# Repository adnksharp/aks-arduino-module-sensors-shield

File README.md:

# AKS AMSS | Arduino Module Sensors Shield

Shield configurable para modulos de sensores de Arduino a cajas de contactos

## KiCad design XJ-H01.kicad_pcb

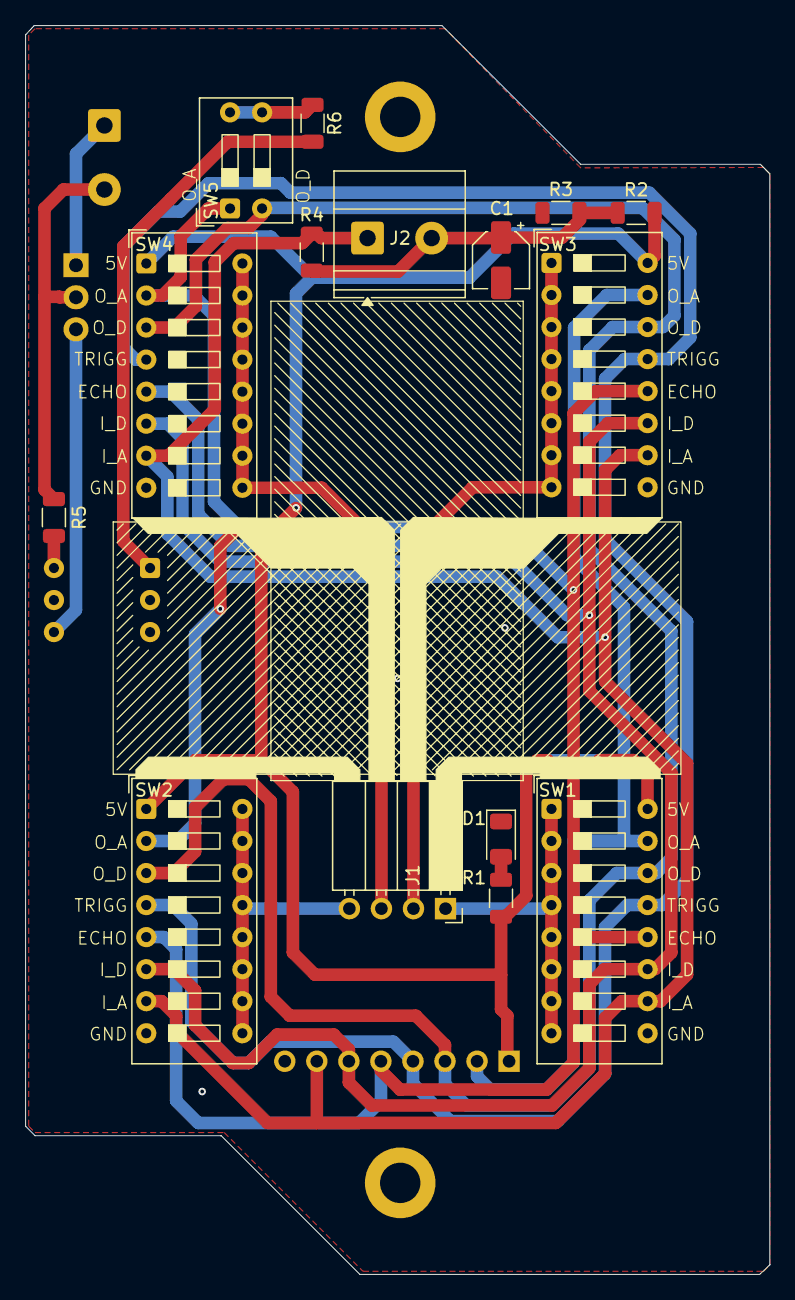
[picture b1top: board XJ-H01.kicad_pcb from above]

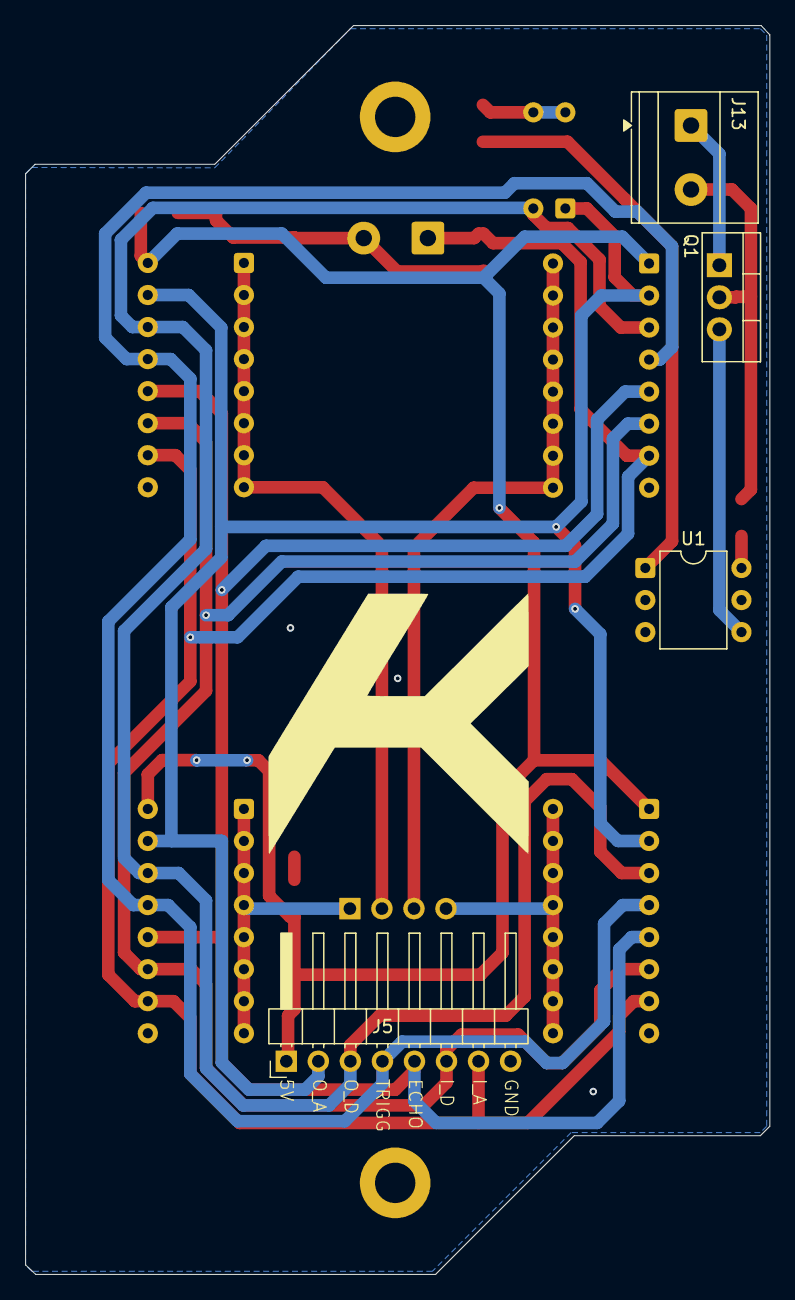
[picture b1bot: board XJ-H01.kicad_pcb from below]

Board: 2 copper layers, 59.0 x 99.0 mm, 22 parts (5 on the bottom side), 20 nets.

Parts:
C1: 47u; CP_Elec_4x3.9
D1: LED; LED_1206_3216Metric
G0: LOGO; logog
J1: 01x04; PinSocket_1x04_P2.54mm_Horizontal
J2: SCT_013; TerminalBlock_Phoenix_MKDS-1,5-2-5.08_1x02_P5.08mm_Horizont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
J5: P_01x08; PinHeader_1x08_P2.54mm_Horizontal
J13: AC; TerminalBlock_Phoenix_MKDS-1,5-2-5.08_1x02_P5.08mm_Horizont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
MX1, MX2: MountingHole_3.2mm_M3_DIN965_Pad
Q1: BT139-600; TO-220-3_Vertical
R1: 220; R_1206_3216Metric
R2, R3: 10k; R_1206_3216Metric
R4, R6: 330; R_1206_3216Metric
R5: 180; R_1206_3216Metric
SW1, SW2, SW3, SW4: SW_DIP_x08; SW_DIP_SPSTx08_Slide_9.78x22.5mm_W7.62mm_P2.54mm
SW5: SW_DIP_x02; SW_DIP_SPSTx02_Slide_9.78x7.26mm_W7.62mm_P2.54mm
U1: MOC3011M; DIP-6_W7.62mm

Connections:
+5V: J5.1, R1.2, R2.2, SW1.16, SW2.1, SW3.16, SW4.1
AC_L: J13.1, Q1.1 (A1)
AC_SW: J13.2, Q1.2 (A2), R5.2
Earth: C1.2, D1.1 (K), J5.8, R3.1, SW1.9, SW2.8, SW3.9, SW4.8, U1.2
I_A: J2.1, J5.7, R4.2, SW1.10, SW2.7, SW3.10, SW4.7
I_D: J5.6, SW1.11, SW2.6, SW3.11, SW4.6
LB: C1.1, J2.2, R2.1, R3.2, R4.1
unnamed: D1.2 (A), R1.1
unnamed: J1.1, SW1.1, SW1.2, SW1.3, SW1.4, SW1.5, SW1.6, SW1.7, SW1.8
unnamed: J1.2, SW3.1, SW3.2, SW3.3, SW3.4, SW3.5, SW3.6, SW3.7, SW3.8
unnamed: J1.3, SW4.9, SW4.10, SW4.11, SW4.12, SW4.13, SW4.14, SW4.15, SW4.16
unnamed: J1.4, SW2.9, SW2.10, SW2.11, SW2.12, SW2.13, SW2.14, SW2.15, SW2.16
unnamed: Q1.3 (G), U1.4
unnamed: R5.1, U1.6
unnamed: R6.1, SW5.3, SW5.4
unnamed: R6.2, U1.1
O_A: J5.2, SW1.15, SW2.2, SW3.15, SW4.2, SW5.1
O_D: J5.3, SW1.14, SW2.3, SW3.14, SW4.3, SW5.2
S_E: J5.5, SW1.12, SW2.5, SW3.12, SW4.5
S_T: J5.4, SW1.13, SW2.4, SW3.13, SW4.4

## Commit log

2026-02-03 chore (.): init git prj
2026-02-03 feat (XJ-H01): init Kicad project
2026-02-03 feat (XJ-H01): add Kicad PCB
2026-02-03 chore (.gitignore): add Kicad cache to git ignored
2026-02-03 feat (XJ-H01): add Kicad sensors scheme
2026-02-03 chore (.gitignore): add Kicad backups to git ignored
2026-02-03 feat (XJ-H01): add logo to Kicad
2026-02-03 feat (XJ-H01): add Kicad main scheme
2026-02-03 chore (img): add 3D PCB Kicad result
2026-02-03 docs (README): add imgs to markdown repo
2026-02-03 chore (.step): add PCB step files
2026-02-03 chore (img): add change component position for tentative resize PCB
2026-02-03 chore (XJ-H01): add change component position for tentative resize PCB
2026-02-03 chore (.step): add PCB+box step files
2026-02-03 chore (img): update screenshots
